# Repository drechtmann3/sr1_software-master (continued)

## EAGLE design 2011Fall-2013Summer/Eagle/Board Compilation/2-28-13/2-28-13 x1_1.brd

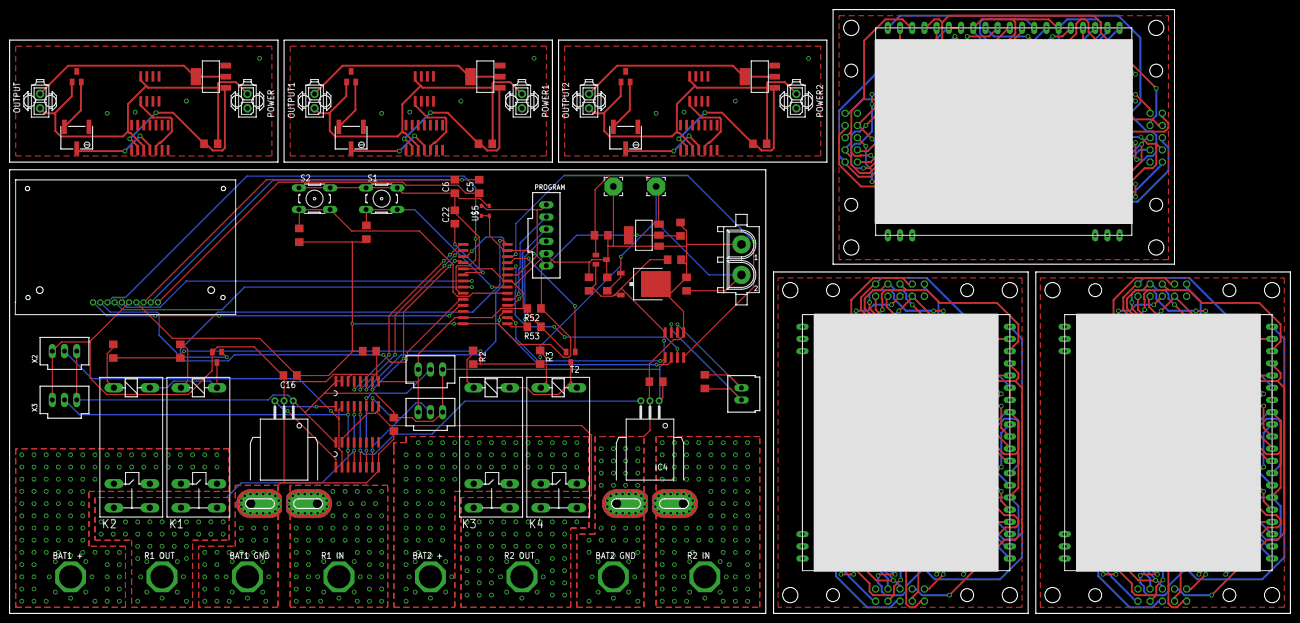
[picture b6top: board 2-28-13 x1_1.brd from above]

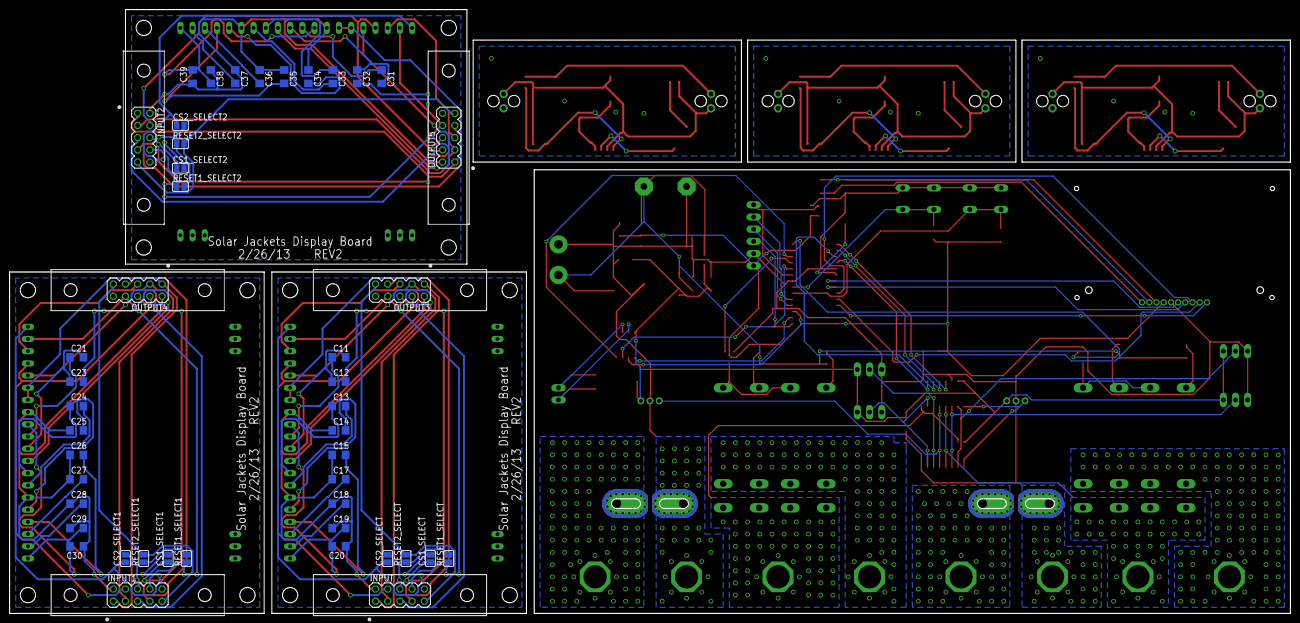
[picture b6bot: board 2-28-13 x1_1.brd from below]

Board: 2 copper layers, 266.7 x 125.7 mm, 130 parts (45 on the bottom side), 136 nets.

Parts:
BAT+_1: BAT1 +; SOLDERPAD
BAT+_2: BAT2 +; SOLDERPAD
BAT-_1: BAT1 GND; SOLDERPAD
BAT-_2: BAT2 GND; SOLDERPAD
C1: .3uF; C1206
C2, C3, C4, C5, C6, C7, C8, C9, C10, C11, C12, C13, C14, C15, C17, C18, C19, C20, C21, C22, C23, C24, C25, C26, C27, C28, C29, C30, C31, C32, C33, C34, C35, C36, C37, C38, C39: 1uF; C1206
C16, C48: .1uF; C1206
CS1_SELECT, CS1_SELECT1, CS1_SELECT2, CS2_SELECT, CS2_SELECT1, CS2_SELECT2: SJ
IC1: 7805DT; TO252
IC2, IC4: ACS758ECB-200B-PFF-T; CB-PFF
IC3: REG1117; SOT223
IC5, IC6, IC7: LM339D; SO14
IC8, IC9, IC10: EADOGM128
INPUT, INPUT1, INPUT2: AMP_LATCH_10; MA05-2
J1: 350428-1
K1, K2, K3, K4: G2REA
OUTPUT, OUTPUT1, OUTPUT2: 794681-2
OUTPUT3, OUTPUT4, OUTPUT5: AMP_LATCH_10; MA05-2
PAD_12V: 12v; 3,81/1,4
PAD_GND: gnd; 3,81/1,4
POWER, POWER1, POWER2: 794681-2
PROGRAM: C-GRID-06-70543; 70543-06
R1, R2, R3, R4, R5, R169: 1K; R1206
R6: 120; R1206
R7, R8, R9: 10k; RTRIMTS63Y
R52: 10k\; R1206
R53: 470; R1206
RESET1_SELECT, RESET1_SELECT1, RESET1_SELECT2, RESET2_SELECT, RESET2_SELECT1, RESET2_SELECT2: SJ
R_IN_1: R1 IN; SOLDERPAD
R_IN_2: R2 IN; SOLDERPAD
R_OUT_1: R1 OUT; SOLDERPAD
R_OUT_2: R2 OUT; SOLDERPAD
S1, S2: B3F-10XX
T1, T2: PMV56XN; SOT23
U$1: MCP-3008; SO16
U$2: LCD_SCREEN
U$3: SP720APP; SO16
U$4: PIC24HJ128GP-202; SO28W
U$5: ASE
U$6: MAX6105; SOT23
U$7: MAX3440E; SO-08
U$8, U$12, U$16: 100; R1206
U$9, U$13, U$17: MAX6103; SOT23
U$10, U$14, U$18: NDT3055; SOT223
U$11, U$15, U$19: LM35; SO-08
X1: BAT2 TEMP 1; 70543-03
X2: BAT1 TEMP1; 70543-03
X3: BAT1 TEMP2; 70543-03
X4: BAT2 TEMP2; 70543-03
X5: rs-485; 70543-02

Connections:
3.3V: IC8.34, IC8.35, INPUT.1, OUTPUT3.1
3.3V1: IC9.34, IC9.35, INPUT1.1, OUTPUT4.1
3.3V2: IC10.34, IC10.35, INPUT2.1, OUTPUT5.1
12V: IC5.3, OUTPUT.1, POWER.2, U$8.2, U$9.1, U$11.8
12V1: IC6.3, OUTPUT1.1, POWER1.2, U$12.2, U$13.1, U$15.8
12V2: IC7.3, OUTPUT2.1, POWER2.2, U$16.2, U$17.1, U$19.8
+3V3: C9.1, C16.1, C48.1, IC3.2, PROGRAM.6, R4.2, R5.1, R52.1, U$2.7, U$4.13, U$4.28, U$5.1, U$5.4
+5V: C3.2, C4.1, C7.1, C10.2, IC1.2, IC2.1, IC4.1, U$1.15, U$1.16, U$3.16, U$6.2, U$7.8, X1.3, X2.3, X3.3, X4.3
+12V: C1.1, C2.1, C8.1, IC1.1, IC3.3, J1.2, PAD_12V.1, R1.2, R2.2, R3.2, R169.2, U$6.1
A0: IC8.38, INPUT.5, OUTPUT3.5
A1: IC9.38, INPUT1.5, OUTPUT4.5
A2: IC10.38, INPUT2.5, OUTPUT5.5
CH0: IC2.3, U$1.1, U$3.1
CH1: U$1.2, U$3.2, X2.2
CH2: U$1.3, U$3.3, X3.2
CH3: K1.S, K1.S@, K2.S, K2.S@, R_OUT_1.P$1, U$1.4, U$3.4
CH4: IC4.3, U$1.5, U$3.5
CH5: U$1.6, U$3.6, X1.2
CH6: U$1.7, U$3.7, X4.2
CH7: K3.S, K3.S@, K4.S, K4.S@, R_OUT_2.P$1, U$1.8, U$3.15
CS1: CS1_SELECT.1, INPUT.6, OUTPUT3.6
CS2: CS2_SELECT.2, INPUT.7, OUTPUT3.7
CS3: CS1_SELECT1.1, INPUT1.6, OUTPUT4.6
CS4: CS2_SELECT1.2, INPUT1.7, OUTPUT4.7
CS5: CS1_SELECT2.1, INPUT2.6, OUTPUT5.6
CS6: CS2_SELECT2.2, INPUT2.7, OUTPUT5.7
CS_SLCT: CS1_SELECT.2, CS2_SELECT.1, IC8.40
CS_SLCT1: CS1_SELECT1.2, CS2_SELECT1.1, IC9.40
CS_SLCT2: CS1_SELECT2.2, CS2_SELECT2.1, IC10.40
GND: BAT-_1.P$1, BAT-_2.P$1, C1.2, C2.2, C3.1, C4.2, C6.1, C7.2, C8.2, C9.2, C10.1, C16.2, C22.2, C48.2, IC1.3, IC2.2, IC2.IP+, IC2.IP+@2, IC2.IP+@3, IC2.IP+@4, IC2.IP+@5, IC2.IP+@6, IC2.IP+@7, IC2.IP+@8, IC2.IP+@9, IC2.IP+@10, IC2.IP+@11, IC2.IP+@12, IC2.IP+@13, IC2.IP+@14, IC2.IP+@15, IC2.IP+@16, IC2.IP+@17, IC3.1, IC4.2, IC4.IP+, IC4.IP+@2, IC4.IP+@3, IC4.IP+@4, IC4.IP+@5, IC4.IP+@6, IC4.IP+@7, IC4.IP+@8, IC4.IP+@9, IC4.IP+@10, IC4.IP+@11, IC4.IP+@12, IC4.IP+@13, IC4.IP+@14, IC4.IP+@15, IC4.IP+@16, IC4.IP+@17, J1.1, PAD_GND.1, PROGRAM.5, R52.2, R53.1, S1.1, S1.2, S2.1, S2.2, T1.2, T2.2, U$1.9, U$1.14, U$2.6, U$3.8, U$4.8, U$4.19, U$4.27, U$5.2, U$6.3, U$7.5, X1.1, X2.1, X3.1, X4.1
GND1: IC5.12, POWER.1, R7.1, U$9.3, U$10.3, U$11.4
GND2: IC6.12, POWER1.1, R8.1, U$13.3, U$14.3, U$15.4
GND3: IC7.12, POWER2.1, R9.1, U$17.3, U$18.3, U$19.4
GND4: C14.1, C15.1, C17.1, C18.1, C19.1, C20.1, IC8.26, IC8.33, INPUT.2, OUTPUT3.2
GND5: C25.1, C26.1, C27.1, C28.1, C29.1, C30.1, IC9.26, IC9.33, INPUT1.2, OUTPUT4.2
GND6: C34.1, C35.1, C36.1, C37.1, C38.1, C39.1, IC10.26, IC10.33, INPUT2.2, OUTPUT5.2
MCLR: PROGRAM.4, R53.2, U$4.1
unnamed: K1.2, K2.2, T1.3
unnamed: K2.1, R1.1
unnamed: BAT+_2.P$1, K3.P, K3.P@, K4.P, K4.P@
unnamed: K3.1, R2.1
unnamed: K3.2, K4.2, T2.3
unnamed: K4.1, R3.1
unnamed: IC4.IP-, IC4.IP-@2, IC4.IP-@3, IC4.IP-@4, IC4.IP-@5, IC4.IP-@6, IC4.IP-@7, IC4.IP-@8, IC4.IP-@9, IC4.IP-@10, IC4.IP-@11, IC4.IP-@12, IC4.IP-@13, IC4.IP-@14, IC4.IP-@15, IC4.IP-@16, IC4.IP-@17, R_IN_2.P$1
unnamed: IC2.IP-, IC2.IP-@2, IC2.IP-@3, IC2.IP-@4, IC2.IP-@5, IC2.IP-@6, IC2.IP-@7, IC2.IP-@8, IC2.IP-@9, IC2.IP-@10, IC2.IP-@11, IC2.IP-@12, IC2.IP-@13, IC2.IP-@14, IC2.IP-@15, IC2.IP-@16, IC2.IP-@17, R_IN_1.P$1
unnamed: C6.2, U$2.8
unnamed: C5.2, U$2.9
unnamed: C5.1, U$2.10
unnamed: IC5.2, U$8.1, U$10.1
unnamed: C22.1, U$4.20
unnamed: IC5.4, R7.2
unnamed: R7.3, U$9.2
unnamed: OUTPUT.2, U$10.2, U$10.4
unnamed: IC5.5, U$11.1
unnamed: IC6.2, U$12.1, U$14.1
unnamed: IC6.4, R8.2
unnamed: R8.3, U$13.2
unnamed: OUTPUT1.2, U$14.2, U$14.4
unnamed: IC6.5, U$15.1
unnamed: IC7.2, U$16.1, U$18.1
unnamed: IC7.4, R9.2
unnamed: R9.3, U$17.2
unnamed: OUTPUT2.2, U$18.2, U$18.4
unnamed: IC7.5, U$19.1
unnamed: C11.2, C12.1, IC8.30
unnamed: C11.1, IC8.31
unnamed: C12.2, IC8.29
unnamed: C13.2, IC8.27
unnamed: C13.1, IC8.28
unnamed: C14.2, IC8.25
unnamed: C15.2, IC8.24
unnamed: C17.2, IC8.23
unnamed: C18.2, IC8.22
unnamed: C19.2, IC8.21
unnamed: C20.2, IC8.32
unnamed: C21.2, C23.1, IC9.30
unnamed: C21.1, IC9.31
unnamed: C23.2, IC9.29
unnamed: C24.2, IC9.27
unnamed: C24.1, IC9.28
unnamed: C25.2, IC9.25
unnamed: C26.2, IC9.24
unnamed: C27.2, IC9.23
unnamed: C28.2, IC9.22
unnamed: C29.2, IC9.21
unnamed: C30.2, IC9.32
unnamed: C31.2, C32.1, IC10.30
unnamed: C31.1, IC10.31
unnamed: C32.2, IC10.29
unnamed: K1.1, R169.1
unnamed: C33.2, IC10.27
unnamed: C33.1, IC10.28
unnamed: C34.2, IC10.25
unnamed: C35.2, IC10.24
unnamed: C36.2, IC10.23
unnamed: C37.2, IC10.22
unnamed: C38.2, IC10.21
unnamed: C39.2, IC10.32
unnamed: R6.2, U$7.7, X5.1
unnamed: R6.1, U$7.6, X5.2
unnamed: BAT+_1.P$1, K1.P, K1.P@, K2.P, K2.P@
OSC1: PROGRAM.1, U$4.9, U$5.3
PGEC1: PROGRAM.2, U$4.5
PGED1: PROGRAM.3, U$4.4
RA0: U$4.2, U$7.1
RA1: U$4.3, U$7.2
RA3: U$4.10, U$7.3
RA4: U$4.12, U$7.4
RB2: R5.2, S2.3, S2.4, U$4.6
RB3: R4.1, S1.3, S1.4, U$4.7
RB4: T2.1, U$4.11
RB5: T1.1, U$4.14
RB6: U$1.13, U$4.15
RB7: U$1.12, U$4.16
RB8: U$1.11, U$4.17
RB9: U$1.10, U$4.18
RB10: U$2.5, U$4.21
RB11: U$2.4, U$4.22
RB12: U$2.3, U$4.23
RB13: U$2.2, U$4.24
RB14: U$2.1, U$4.25
RESET1: IC8.39, INPUT.8, OUTPUT3.8, RESET1_SELECT.1
RESET2: INPUT.9, OUTPUT3.9, RESET2_SELECT.2
RESET3: IC9.39, INPUT1.8, OUTPUT4.8, RESET1_SELECT1.1
RESET4: INPUT1.9, OUTPUT4.9, RESET2_SELECT1.2
RESET5: IC10.39, INPUT2.8, OUTPUT5.8, RESET1_SELECT2.1
RESET6: INPUT2.9, OUTPUT5.9, RESET2_SELECT2.2
RESET_SLCT: RESET1_SELECT.2, RESET2_SELECT.1
RESET_SLCT1: RESET1_SELECT1.2, RESET2_SELECT1.1
RESET_SLCT2: RESET1_SELECT2.2, RESET2_SELECT2.1
SCL: IC8.37, INPUT.4, OUTPUT3.4
SCL1: IC9.37, INPUT1.4, OUTPUT4.4
SCL2: IC10.37, INPUT2.4, OUTPUT5.4
SI: IC8.36, INPUT.3, OUTPUT3.3
SI1: IC9.36, INPUT1.3, OUTPUT4.3
SI2: IC10.36, INPUT2.3, OUTPUT5.3

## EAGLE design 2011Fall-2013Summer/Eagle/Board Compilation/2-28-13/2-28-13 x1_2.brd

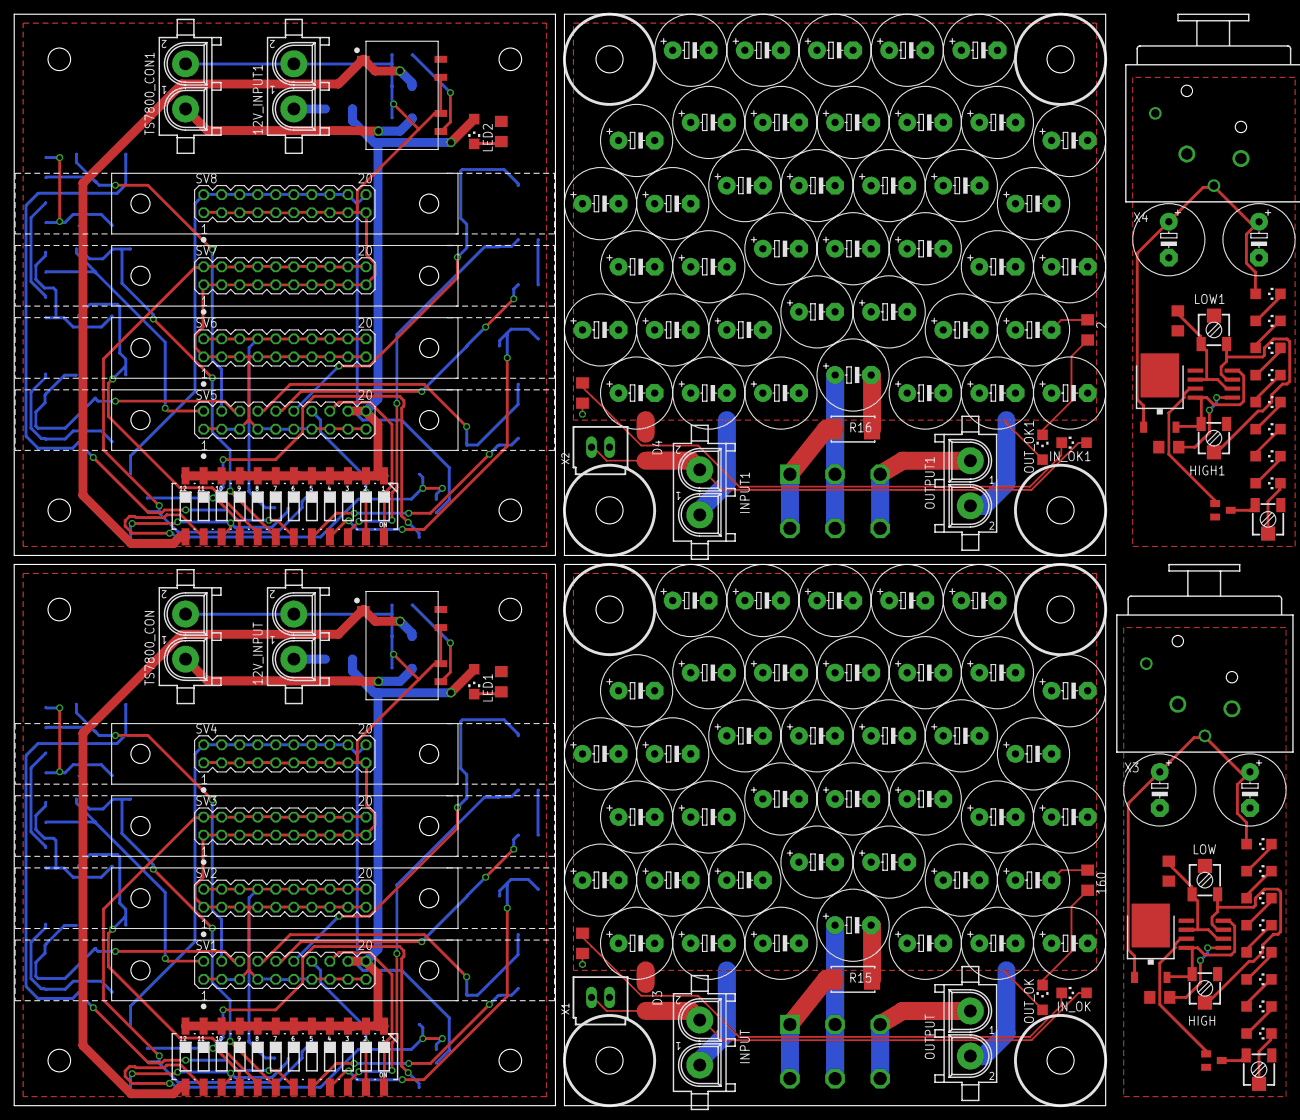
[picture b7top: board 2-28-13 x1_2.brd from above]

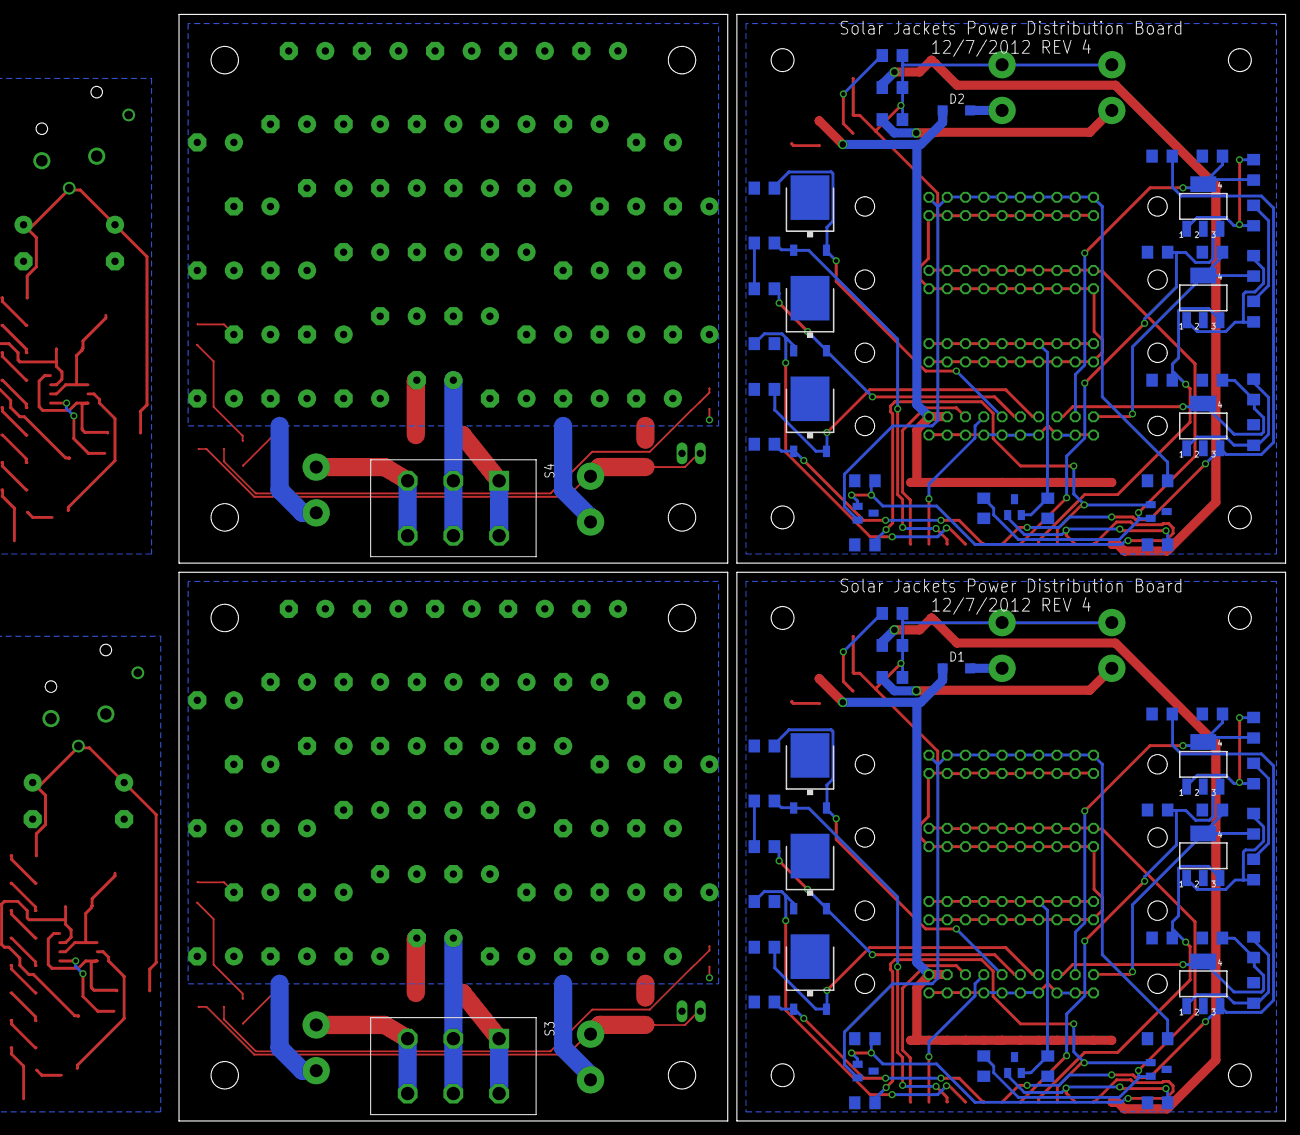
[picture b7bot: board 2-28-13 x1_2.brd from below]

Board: 2 copper layers, 153.7 x 153.7 mm, 232 parts (76 on the bottom side), 106 nets.

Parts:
1, 3: 160; R1206
1K, 1K1: 10 k; RTRIM3314J
2, 160: R1206
3V1, 3V2, 3V3, 3V4, 3V5, 3V6: MAX6103; SOT23
12V_INPUT, 12V_INPUT1: 350759-4
317CAP1, 317CAP3, 317CAP4, 317CAP6, 317CAP9, 317CAP11: .33uF; C1206
317CAP2, 317CAP5, 317CAP7, 317CAP8, 317CAP10, 317CAP12, 6103CAP1, 6103CAP2, 6103CAP3, 6103CAP4, 6103CAP5, 6103CAP6, 6103CAP7, 6103CAP8, 6103CAP9, 6103CAP10, 6103CAP11, 6103CAP12: 1uF; C1206
C1, C2, C3, C4, C5, C6, C7, C8, C9, C10, C11, C12: 1uF; C1206
C13, C14, C15, C16, C17, C18, C19, C20, C21, C22, C23, C24, C25, C26, C27, C28, C29, C30, C31, C32, C33, C34, C35, C36, C37, C38, C39, C40, C41, C42, C43, C44, C45, C46, C47, C48, C49, C50, C51, C52, C53, C54, C55, C56, C57, C58, C59, C60, C61, C62, C63, C64, C65, C66, C67, C68, C69, C70, C71, C72, C73, C74, C75, C76, C77, C78, C79, C80, C81, C82, C83, C84, C85, C86, C87, C88, C89, C90, C91, C92: E5-10,5
C93, C97: 100uF; C1206
C94, C98: 10nF; C1206
C95, C96, C99, C100: 2.2F; E5-10,5
D1, D2, D3, D4: SOD123
HIGH, HIGH1: 10k; RTRIM3314J
IC1, IC2, IC3, IC4, IC5, IC6: LM317; SOT223
IC7, IC9: 7805DT; TO252
IC8, IC10: LM555D; SO08
INPUT, INPUT1: 350428-1
IN_OK, IN_OK1: CHIPLED_1206
LED1, LED2, LED3, LED4, LED5, LED6, LED7, LED8, LED9, LED10, LED11, LED12, LED13, LED14, LED15, LED16, LED17, LED18: CHIPLED_1206
LOW, LOW1: 10k; RTRIM3314J
OUTPUT, OUTPUT1: 350428-1
OUT_OK, OUT_OK1: CHIPLED_1206
PWR_1, PWR_2, PWR_3, PWR_4, PWR_5, PWR_6: 7805DT; TO252
R1, R14: 430; R1206
R2, R4, R6, R7, R9, R11: 220; R1206
R3, R5, R8, R10, R12, R13: 361; R1206
R15, R16: 50 1W; WSC2515
S1, S2: 219-12; CTS-219-12
S3, S4: SLIDE_SWITCH
SV1, SV2, SV3, SV4, SV5, SV6, SV7, SV8: AMPLATCH-20; MA10-2
TS7800_CON, TS7800_CON1: 350759-4
U$1, U$2: V7805
U$3, U$4: PMV56XN215; SOT23
V7805_C1, V7805_C2, V7805_C3, V7805_C4, V7805_C5, V7805_C6: 1uF; C1206
X1, X2: C-GRID-02-70543; 70543-02
X3, X4: NC3FAH2

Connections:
3.3V1: 317CAP8.1, IC4.4, R7.1, SV1.6
3.3V1_EN: 317CAP3.1, IC4.3, S1.19
3.3V1_EN1: 317CAP1.1, IC1.3, S2.19
3.3V2: 317CAP10.1, IC5.4, R9.1, SV1.4
3.3V2_EN: 317CAP9.1, IC5.3, S1.18
3.3V2_EN1: 317CAP4.1, IC2.3, S2.18
3.3V3: 317CAP12.1, IC6.4, R11.1, SV1.2
3.3V3_EN: 317CAP11.1, IC6.3, S1.17
3.3V3_EN1: 317CAP6.1, IC3.3, S2.17
3.3V4: 317CAP7.1, IC3.4, R6.1, SV5.2
3.3V5: 317CAP2.1, IC1.4, R2.1, SV5.6
3.3V6: 317CAP5.1, IC2.4, R4.1, SV5.4
5V: C13.+, C14.+, C15.+, C16.+, C17.+, C18.+, C19.+, C20.+, C21.+, C22.+, C23.+, C24.+, C25.+, C26.+, C27.+, C28.+, C29.+, C30.+, C31.+, C32.+, C33.+, C34.+, C35.+, C36.+, C37.+, C38.+, C39.+, C40.+, C41.+, C42.+, C43.+, C44.+, C45.+, C46.+, C47.+, C48.+, C49.+, C50.+, C51.+, C52.+, D3.C, OUT_OK.A, S3.2, S3.5
5V1: C2.1, PWR_1.2, SV1.12
5V1_EN: C1.1, PWR_1.1, S1.22
5V1_EN1: C7.1, PWR_4.1, S2.22
5V2: C4.1, PWR_2.2, SV1.10
5V2_EN: C3.1, PWR_2.1, S1.21
5V2_EN1: C9.1, PWR_5.1, S2.21
5V3: C6.1, PWR_3.2, SV1.8
5V3_EN: C5.1, PWR_3.1, S1.20
5V3_EN1: C12.1, PWR_6.1, S2.20
5V4: C11.1, PWR_6.2, SV5.8
5V5: C10.1, PWR_5.2, SV5.10
5V6: C8.1, PWR_4.2, SV5.12
5V7: C53.+, C54.+, C55.+, C56.+, C57.+, C58.+, C59.+, C60.+, C61.+, C62.+, C63.+, C64.+, C65.+, C66.+, C67.+, C68.+, C69.+, C70.+, C71.+, C72.+, C73.+, C74.+, C75.+, C76.+, C77.+, C78.+, C79.+, C80.+, C81.+, C82.+, C83.+, C84.+, C85.+, C86.+, C87.+, C88.+, C89.+, C90.+, C91.+, C92.+, D4.C, OUT_OK1.A, S4.2, S4.5
12V: D1.C, LED1.A, S1.1, S1.2, S1.3, S1.4, S1.5, S1.6, S1.7, S1.8, S1.9, S1.10, S1.11, S1.12, SV1.18, SV1.20
12V1: D2.C, LED2.A, S2.1, S2.2, S2.3, S2.4, S2.5, S2.6, S2.7, S2.8, S2.9, S2.10, S2.11, S2.12, SV5.18, SV5.20
12V1_EN: S1.24, SV1.16
12V1_EN1: S2.24, SV5.16
12V2_EN: S1.23, SV1.14
12V2_EN1: S2.23, SV5.14
24V: C95.+, C96.+, IC7.1, LED3.A, X3.3
24V1: C99.+, C100.+, IC9.1, LED11.A, X4.3
+5V: HIGH.3, IC7.2, IC8.4, IC8.8
+5V1: HIGH1.3, IC9.2, IC10.4, IC10.8
GND: 3V3.3, 3V4.3, 3V5.3, 12V_INPUT.2, 317CAP3.2, 317CAP8.2, 317CAP9.2, 317CAP10.2, 317CAP11.2, 317CAP12.2, 6103CAP7.2, 6103CAP8.2, 6103CAP9.2, 6103CAP10.2, 6103CAP11.2, 6103CAP12.2, C1.2, C2.2, C3.2, C4.2, C5.2, C6.2, PWR_1.3, PWR_2.3, PWR_3.3, R1.2, R8.2, R10.2, R12.2, SV1.1, SV1.3, SV1.5, SV1.7, SV1.9, SV1.11, SV1.13, SV1.15, SV1.17, SV1.19, SV2.1, SV2.3, SV2.5, SV2.7, SV2.9, SV2.11, SV2.13, SV2.15, SV2.17, SV2.19, SV3.1, SV3.3, SV3.5, SV3.7, SV3.9, SV3.11, SV3.13, SV3.15, SV3.17, SV3.19, SV4.1, SV4.3, SV4.5, SV4.7, SV4.9, SV4.11, SV4.13, SV4.15, SV4.17, SV4.19, TS7800_CON.2, U$2.7, U$2.9, V7805_C4.2, V7805_C5.2, V7805_C6.2
GND1: 3V1.3, 3V2.3, 3V6.3, 12V_INPUT1.2, 317CAP1.2, 317CAP2.2, 317CAP4.2, 317CAP5.2, 317CAP6.2, 317CAP7.2, 6103CAP1.2, 6103CAP2.2, 6103CAP3.2, 6103CAP4.2, 6103CAP5.2, 6103CAP6.2, C7.2, C8.2, C9.2, C10.2, C11.2, C12.2, PWR_4.3, PWR_5.3, PWR_6.3, R3.2, R5.2, R13.2, R14.2, SV5.1, SV5.3, SV5.5, SV5.7, SV5.9, SV5.11, SV5.13, SV5.15, SV5.17, SV5.19, SV6.1, SV6.3, SV6.5, SV6.7, SV6.9, SV6.11, SV6.13, SV6.15, SV6.17, SV6.19, SV7.1, SV7.3, SV7.5, SV7.7, SV7.9, SV7.11, SV7.13, SV7.15, SV7.17, SV7.19, SV8.1, SV8.3, SV8.5, SV8.7, SV8.9, SV8.11, SV8.13, SV8.15, SV8.17, SV8.19, TS7800_CON1.2, U$1.7, U$1.9, V7805_C1.2, V7805_C2.2, V7805_C3.2
GND2: 1.1, 160.1, C13.-, C14.-, C15.-, C16.-, C17.-, C18.-, C19.-, C20.-, C21.-, C22.-, C23.-, C24.-, C25.-, C26.-, C27.-, C28.-, C29.-, C30.-, C31.-, C32.-, C33.-, C34.-, C35.-, C36.-, C37.-, C38.-, C39.-, C40.-, C41.-, C42.-, C43.-, C44.-, C45.-, C46.-, C47.-, C48.-, C49.-, C50.-, C51.-, C52.-, INPUT.1, OUTPUT.2, R15.2
GND3: 2.1, 3.1, C53.-, C54.-, C55.-, C56.-, C57.-, C58.-, C59.-, C60.-, C61.-, C62.-, C63.-, C64.-, C65.-, C66.-, C67.-, C68.-, C69.-, C70.-, C71.-, C72.-, C73.-, C74.-, C75.-, C76.-, C77.-, C78.-, C79.-, C80.-, C81.-, C82.-, C83.-, C84.-, C85.-, C86.-, C87.-, C88.-, C89.-, C90.-, C91.-, C92.-, INPUT1.1, OUTPUT1.2, R16.2
GND4: C93.2, C94.2, C95.-, C96.-, IC7.3, IC8.1, U$3.2, X3.1
GND5: C97.2, C98.2, C99.-, C100.-, IC9.3, IC10.1, U$4.2, X4.1
unnamed: U$2.6, V7805_C4.1
unnamed: LED1.C, R1.1
unnamed: 12V_INPUT.1, D1.A
unnamed: IC1.1, R2.2, R3.1
unnamed: IC2.1, R4.2, R5.1
unnamed: IC3.1, R6.2, R13.1
unnamed: U$1.6, V7805_C1.1
unnamed: LED2.C, R14.1
unnamed: 12V_INPUT1.1, D2.A
unnamed: 160.2, OUT_OK.C
unnamed: OUTPUT.1, S3.3, S3.4
unnamed: IC4.1, R7.2, R8.1
unnamed: IC5.1, R9.2, R10.1
unnamed: IC6.1, R11.2, R12.1
unnamed: D3.A, INPUT.2, IN_OK.A, X1.1
unnamed: R15.1, S3.1, S3.6
unnamed: 1.2, IN_OK.C
unnamed: 2.2, OUT_OK1.C
unnamed: OUTPUT1.1, S4.3, S4.4
unnamed: D4.A, INPUT1.2, IN_OK1.A, X2.1
unnamed: R16.1, S4.1, S4.6
unnamed: 3.2, IN_OK1.C
unnamed: LED3.C, LED4.A
unnamed: LED4.C, LED5.A
unnamed: LED5.C, LED6.A
unnamed: LED6.C, LED7.A
unnamed: LED7.C, LED9.A
unnamed: LED8.A, LED9.C
unnamed: LED8.C, LED10.A
unnamed: 1K.2, LED10.C
unnamed: HIGH.2, IC8.7, LOW.3
unnamed: C93.1, IC8.2, IC8.6, LOW.1
unnamed: C94.1, IC8.5
unnamed: 1K.3, U$3.3
unnamed: IC8.3, U$3.1
unnamed: LED11.C, LED12.A
unnamed: LED12.C, LED13.A
unnamed: LED13.C, LED14.A
unnamed: LED14.C, LED15.A
unnamed: LED15.C, LED17.A
unnamed: LED16.A, LED17.C
unnamed: LED16.C, LED18.A
unnamed: 1K1.2, LED18.C
unnamed: HIGH1.2, IC10.7, LOW1.3
unnamed: C97.1, IC10.2, IC10.6, LOW1.1
unnamed: C98.1, IC10.5
unnamed: 1K1.3, U$4.3
unnamed: IC10.3, U$4.1
TS7800_+: TS7800_CON.1, U$2.5, V7805_C6.1
TS7800_+1: TS7800_CON1.1, U$1.5, V7805_C3.1
TS7800_EN: S1.13, U$2.1, V7805_C5.1
TS7800_EN1: S2.13, U$1.1, V7805_C2.1
VREF1: 3V3.2, 6103CAP8.1, SV3.2, SV3.4, SV3.6, SV3.8, SV3.10, SV3.12, SV3.14, SV3.16, SV3.18, SV3.20
VREF1_EN: 3V3.1, 6103CAP7.1, S1.16
VREF1_EN1: 3V1.1, 6103CAP1.1, S2.16
VREF2: 3V4.2, 6103CAP10.1, SV2.2, SV2.4, SV2.6, SV2.8, SV2.10, SV2.12, SV2.14, SV2.16, SV2.18, SV2.20
VREF2_EN: 3V4.1, 6103CAP9.1, S1.15
VREF2_EN1: 3V2.1, 6103CAP3.1, S2.15
VREF3: 3V5.2, 6103CAP12.1, SV4.2, SV4.4, SV4.6, SV4.8, SV4.10, SV4.12, SV4.14, SV4.16, SV4.18, SV4.20
VREF3_EN: 3V5.1, 6103CAP11.1, S1.14
VREF3_EN1: 3V6.1, 6103CAP5.1, S2.14
VREF4: 3V1.2, 6103CAP2.1, SV7.2, SV7.4, SV7.6, SV7.8, SV7.10, SV7.12, SV7.14, SV7.16, SV7.18, SV7.20
VREF5: 3V2.2, 6103CAP4.1, SV6.2, SV6.4, SV6.6, SV6.8, SV6.10, SV6.12, SV6.14, SV6.16, SV6.18, SV6.20
VREF6: 3V6.2, 6103CAP6.1, SV8.2, SV8.4, SV8.6, SV8.8, SV8.10, SV8.12, SV8.14, SV8.16, SV8.18, SV8.20

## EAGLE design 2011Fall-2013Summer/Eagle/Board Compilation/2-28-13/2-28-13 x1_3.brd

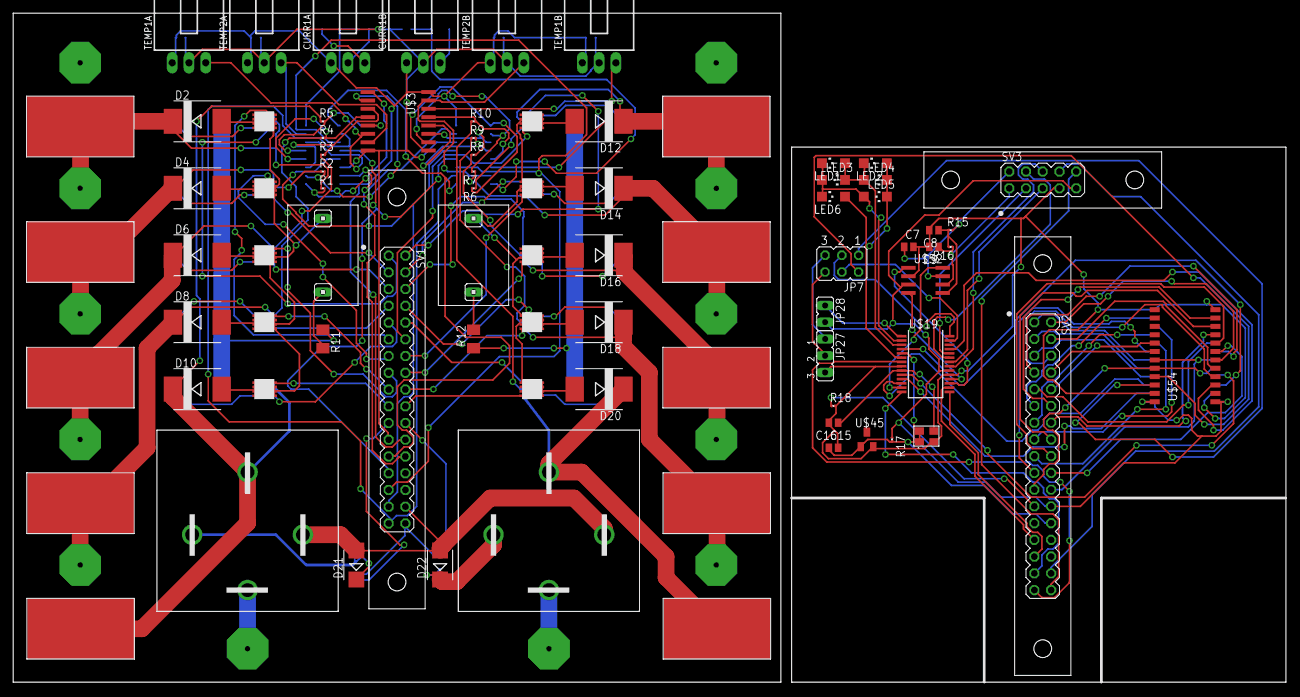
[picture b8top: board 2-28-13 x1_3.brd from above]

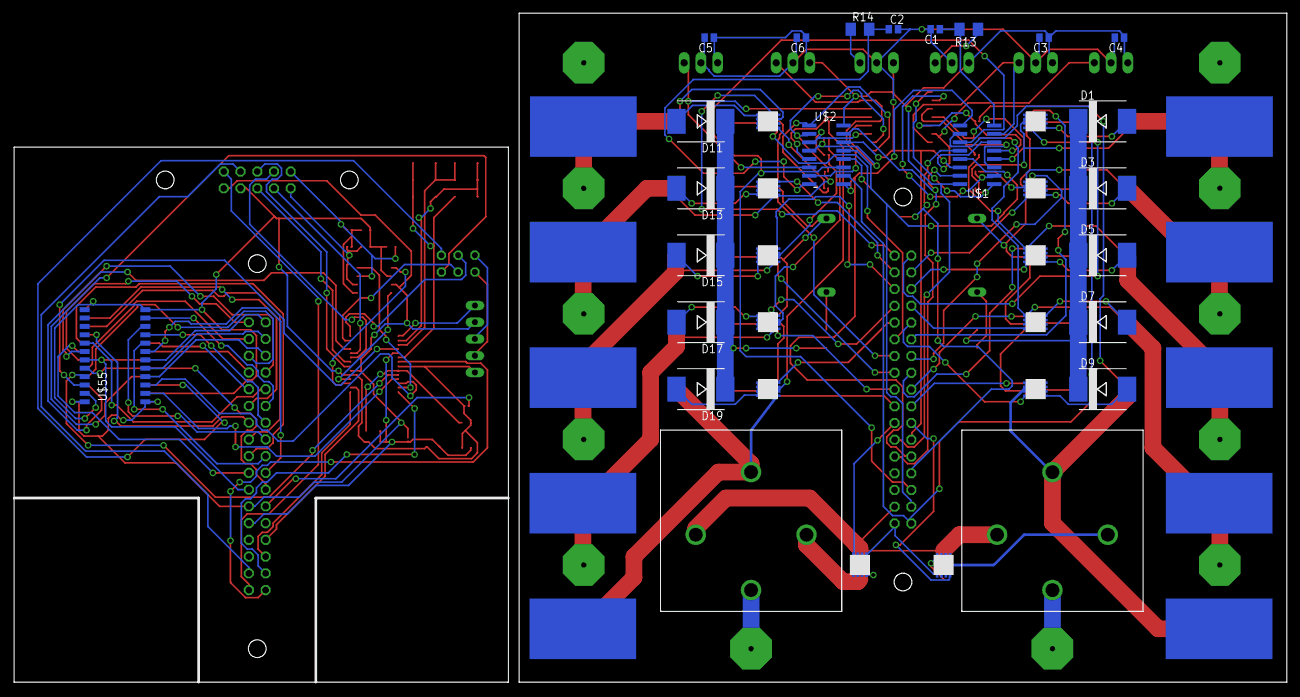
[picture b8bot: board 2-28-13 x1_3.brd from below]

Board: 2 copper layers, 193.1 x 101.5 mm, 126 parts (33 on the bottom side), 148 nets.

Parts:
C1, C2, C3, C4, C5, C6: 0.1uF; C0504
C7, C9: 100pF; C0504
C8: 47nF; C0504
C15: 10nF; C0504
C16: 15pF; C0504
CURR1A, CURR1B: C-GRID-03-70553; 70553-03
D1, D2, D3, D4, D5, D6, D7, D8, D9, D10, D11, D12, D13, D14, D15, D16, D17, D18, D19, D20: SMC
D21, D22: SMB
JP7: JP3Q
JP27: JP2
JP28: JP1
L1, L2: INDUCTOR_SOCKET
LED1, LED2, LED3, LED4, LED5, LED6: CHIPLED_1206
R1, R2, R3, R4, R5, R6, R7, R8, R9, R10: 3.3M; R0201
R11, R12: M1206
R13, R14: 1K; M1206
R15, R16: 1k3; R0201
R17: 150; R0201
R18: 0; R0201
SV1, SV2: MA17-2
SV3: AMP_LATCH_10; MA05-2
TEMP1A, TEMP1B, TEMP2A, TEMP2B: C-GRID-03-70553; 70553-03
U$1, U$2: MCP3008; SOIC16N
U$3: SP720APP; SO16W
U$4, U$5, U$6, U$7, U$8, U$9, U$10, U$11, U$12, U$13, U$23, U$26, U$27, U$30, U$31, U$32, U$33, U$34, U$35, U$36, U$37, U$38: SIS322DNT-T1-GE3POWERPAK1212-8; POWERPAK1212-8
U$14, U$15, U$16, U$17, U$18, U$40, U$41, U$42, U$43, U$44: MOLEXCONN-SCREWHOLE
U$19: PIC18F23K22; SSOP28
U$20, U$22, U$24, U$25, U$28, U$29, U$46, U$47, U$48, U$49, U$50, U$51: MOLEXCONN-SCREWHOLE-NEG
U$21, U$39: PB1039
U$45: LM4040; SOT23
U$52: TJA1040; SO-08
U$53: CTS632
U$54, U$55: CD4514BM96E4; SOIC-24

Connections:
12V+: SV1.34, U$23.SOURCE1, U$23.SOURCE2, U$23.SOURCE3, U$38.SOURCE1, U$38.SOURCE2, U$38.SOURCE3
12V+1: SV2.34, SV3.10
12V-: D21.A, D22.A, SV1.32, U$21.P$2, U$39.P$2
12V-1: SV2.32, SV3.8
AGND_PLANE: C1.2, C2.2, C3.2, C4.2, C5.2, C6.2, CURR1A.2, CURR1B.2, SV1.23, TEMP1A.2, TEMP1B.2, TEMP2A.2, TEMP2B.2, U$1.14, U$2.14, U$3.8
AGND_PLANE1: R18.1, SV2.23
CAN: U$19.13, U$52.8
CANH: C7.1, R15.2, SV3.2, U$52.7
CANL: C9.1, R16.1, SV3.1, U$52.6
CH0A: D2.C, R1.1, U$4.SOURCE1, U$4.SOURCE2, U$4.SOURCE3, U$14.P$1, U$22.P$1
CH0B: D12.C, R6.1, U$26.SOURCE1, U$26.SOURCE2, U$26.SOURCE3, U$40.P$1, U$47.P$1
CH1A: D4.C, R2.1, U$6.SOURCE1, U$6.SOURCE2, U$6.SOURCE3, U$15.P$1, U$24.P$1
CH1B: D14.C, R7.1, U$30.SOURCE1, U$30.SOURCE2, U$30.SOURCE3, U$41.P$1, U$48.P$1
CH2A: D6.C, R3.1, U$8.SOURCE1, U$8.SOURCE2, U$8.SOURCE3, U$16.P$1, U$25.P$1
CH2B: D16.C, R8.1, U$32.SOURCE1, U$32.SOURCE2, U$32.SOURCE3, U$42.P$1, U$49.P$1
CH3A: D8.C, R4.1, U$10.SOURCE1, U$10.SOURCE2, U$10.SOURCE3, U$17.P$1, U$28.P$1
CH3B: D18.C, R9.1, U$34.SOURCE1, U$34.SOURCE2, U$34.SOURCE3, U$43.P$1, U$50.P$1
CH4A: D10.C, R5.1, U$12.SOURCE1, U$12.SOURCE2, U$12.SOURCE3, U$18.P$1, U$21.P$4
CH4B: D20.C, R10.1, U$36.SOURCE1, U$36.SOURCE2, U$36.SOURCE3, U$39.P$4, U$44.P$1
CH5A: TEMP1A.3, U$1.6, U$3.6
CH5B: TEMP1B.3, U$2.6, U$3.14
CH6A: TEMP2A.3, U$1.7, U$3.7
CH6B: TEMP2B.3, U$2.7, U$3.15
CH7A: C1.1, R13.2, U$1.8
CH7B: C2.1, R14.2, U$2.8
CLK: SV1.31, U$1.13, U$2.13
CLK1: SV2.31, U$19.14
CS: SV1.33, U$1.10, U$2.10
CS1: SV2.33, U$19.7
DGND: SV1.25, U$1.9, U$2.9
DIN: SV1.29, U$1.11, U$2.11
DIN1: SV2.29, U$19.15
DOUT: SV1.27, U$1.12, U$2.12
DOUT1: SV2.27, U$19.16
GND: C7.2, C8.2, C9.2, C15.2, C16.2, JP27.3, R18.2, SV3.7, U$19.8, U$19.19, U$45.2, U$52.2, U$53.2, U$54.12, U$54.23, U$55.12, U$55.23
I2C_CS: SV3.6, U$19.21
I2C_SCL: SV3.5, U$19.22
I2C_SDI: SV3.4, U$19.23
I2C_SDO: SV3.3, U$19.24
unnamed: R5.2, U$1.5, U$3.5
unnamed: R4.2, U$1.4, U$3.4
unnamed: R3.2, U$1.3, U$3.3
unnamed: R2.2, U$1.2, U$3.2
unnamed: R1.2, U$1.1, U$3.1
unnamed: CURR1A.3, R13.1
unnamed: CURR1B.3, R14.1
unnamed: D1.A, U$4.DRAIN5, U$4.DRAIN6, U$4.DRAIN7, U$4.DRAIN8, U$4.DRAIN_ALL
unnamed: LED1.A, LED2.C, LED3.C, LED4.A, U$19.3
unnamed: LED1.C, LED3.A, LED5.A, LED6.C, U$19.2
unnamed: R10.2, U$2.5, U$3.13
unnamed: R9.2, U$2.4, U$3.12
unnamed: R8.2, U$2.3, U$3.11
unnamed: R7.2, U$2.2, U$3.10
unnamed: R6.2, U$2.1, U$3.9
unnamed: D2.A, U$5.DRAIN5, U$5.DRAIN6, U$5.DRAIN7, U$5.DRAIN8, U$5.DRAIN_ALL
unnamed: D21.C, U$21.P$3, U$23.DRAIN5, U$23.DRAIN6, U$23.DRAIN7, U$23.DRAIN8, U$23.DRAIN_ALL
unnamed: L1.P$1, R11.2
unnamed: LED2.A, LED4.C, LED5.C, LED6.A, U$19.6
unnamed: U$19.18, U$52.4
unnamed: U$19.17, U$52.1
unnamed: JP28.1, U$19.1
unnamed: D3.A, U$6.DRAIN5, U$6.DRAIN6, U$6.DRAIN7, U$6.DRAIN8, U$6.DRAIN_ALL
unnamed: D4.A, U$7.DRAIN5, U$7.DRAIN6, U$7.DRAIN7, U$7.DRAIN8, U$7.DRAIN_ALL
unnamed: U$21.P$1, U$29.P$1
unnamed: D11.A, U$26.DRAIN5, U$26.DRAIN6, U$26.DRAIN7, U$26.DRAIN8, U$26.DRAIN_ALL
unnamed: D5.A, U$8.DRAIN5, U$8.DRAIN6, U$8.DRAIN7, U$8.DRAIN8, U$8.DRAIN_ALL
unnamed: D6.A, U$9.DRAIN5, U$9.DRAIN6, U$9.DRAIN7, U$9.DRAIN8, U$9.DRAIN_ALL
unnamed: D12.A, U$27.DRAIN5, U$27.DRAIN6, U$27.DRAIN7, U$27.DRAIN8, U$27.DRAIN_ALL
unnamed: U$19.4, U$55.22
unnamed: D7.A, U$10.DRAIN5, U$10.DRAIN6, U$10.DRAIN7, U$10.DRAIN8, U$10.DRAIN_ALL
unnamed: D8.A, U$11.DRAIN5, U$11.DRAIN6, U$11.DRAIN7, U$11.DRAIN8, U$11.DRAIN_ALL
unnamed: D13.A, U$30.DRAIN5, U$30.DRAIN6, U$30.DRAIN7, U$30.DRAIN8, U$30.DRAIN_ALL
unnamed: D9.A, U$12.DRAIN5, U$12.DRAIN6, U$12.DRAIN7, U$12.DRAIN8, U$12.DRAIN_ALL
unnamed: D10.A, U$13.DRAIN5, U$13.DRAIN6, U$13.DRAIN7, U$13.DRAIN8, U$13.DRAIN_ALL
unnamed: D14.A, U$31.DRAIN5, U$31.DRAIN6, U$31.DRAIN7, U$31.DRAIN8, U$31.DRAIN_ALL
unnamed: D15.A, U$32.DRAIN5, U$32.DRAIN6, U$32.DRAIN7, U$32.DRAIN8, U$32.DRAIN_ALL
unnamed: D16.A, U$33.DRAIN5, U$33.DRAIN6, U$33.DRAIN7, U$33.DRAIN8, U$33.DRAIN_ALL
unnamed: U$19.10, U$55.21
unnamed: D17.A, U$34.DRAIN5, U$34.DRAIN6, U$34.DRAIN7, U$34.DRAIN8, U$34.DRAIN_ALL
unnamed: D18.A, U$35.DRAIN5, U$35.DRAIN6, U$35.DRAIN7, U$35.DRAIN8, U$35.DRAIN_ALL
unnamed: D19.A, U$36.DRAIN5, U$36.DRAIN6, U$36.DRAIN7, U$36.DRAIN8, U$36.DRAIN_ALL
unnamed: D20.A, U$37.DRAIN5, U$37.DRAIN6, U$37.DRAIN7, U$37.DRAIN8, U$37.DRAIN_ALL
unnamed: L2.P$2, U$27.SOURCE1, U$27.SOURCE2, U$27.SOURCE3, U$31.SOURCE1, U$31.SOURCE2, U$31.SOURCE3, U$33.SOURCE1, U$33.SOURCE2, U$33.SOURCE3, U$35.SOURCE1, U$35.SOURCE2, U$35.SOURCE3, U$37.SOURCE1, U$37.SOURCE2, U$37.SOURCE3
unnamed: U$39.P$1, U$51.P$1
unnamed: D22.C, U$38.DRAIN5, U$38.DRAIN6, U$38.DRAIN7, U$38.DRAIN8, U$38.DRAIN_ALL, U$39.P$3
unnamed: D11.C, D13.C, D15.C, D17.C, D19.C, R12.1
unnamed: L2.P$1, R12.2
unnamed: U$19.11, U$55.2
unnamed: U$19.12, U$55.3
unnamed: JP7.5, JP27.1
unnamed: JP7.6, JP27.2
unnamed: U$19.25, U$54.3
unnamed: JP7.1, U$54.22
unnamed: JP7.2, U$54.21
unnamed: L1.P$2, U$5.SOURCE1, U$5.SOURCE2, U$5.SOURCE3, U$7.SOURCE1, U$7.SOURCE2, U$7.SOURCE3, U$9.SOURCE1, U$9.SOURCE2, U$9.SOURCE3, U$11.SOURCE1, U$11.SOURCE2, U$11.SOURCE3, U$13.SOURCE1, U$13.SOURCE2, U$13.SOURCE3
unnamed: D1.C, D3.C, D5.C, D7.C, D9.C, R11.1
unnamed: C8.1, R15.1, R16.2, U$52.5
unnamed: C16.1, U$19.9, U$53.3
PGC: JP7.4, U$19.27
PGD: JP7.3, U$19.28
RELAYA: SV1.21, U$23.GATE
RELAYA1: SV2.21, U$54.20, U$55.20
RELAYB: SV1.22, U$38.GATE
RELAYB1: SV2.22, U$54.19, U$55.19
VDD_PLANE: C3.1, C4.1, C5.1, C6.1, CURR1A.1, CURR1B.1, SV1.24, TEMP1A.1, TEMP1B.1, TEMP2A.1, TEMP2B.1, U$1.16, U$2.16, U$3.16
VDD_PLANE1: JP28.2, R17.1, SV2.24, SV3.9, U$19.20, U$52.3, U$54.1, U$54.24, U$55.1, U$55.24
VREF: SV1.26, U$1.15, U$2.15
VREF1: C15.1, R17.2, SV2.26, U$19.5, U$45.1, U$53.1, U$53.4
X0A: SV1.1, U$4.GATE
X0A1: SV2.1, U$55.6
X0B: SV1.2, U$26.GATE
X0B1: SV2.2, U$54.6
X1A: SV1.3, U$6.GATE
X1A1: SV2.3, U$55.5
X1B: SV1.4, U$30.GATE
X1B1: SV2.4, U$54.5
X2A: SV1.5, U$8.GATE
X2A1: SV2.5, U$55.4
X2B: SV1.6, U$32.GATE
X2B1: SV2.6, U$54.4
X3A: SV1.7, U$10.GATE
X3A1: SV2.7, U$55.18
X3B: SV1.8, U$34.GATE
X3B1: SV2.8, U$54.18
X4A: SV1.9, U$12.GATE
X4A1: SV2.9, U$55.17
X4B: SV1.10, U$36.GATE
X4B1: SV2.10, U$54.17
Y0A: SV1.11, U$5.GATE
Y0A1: SV2.11, U$55.11
Y0B: SV1.12, U$27.GATE
Y0B1: SV2.12, U$54.11
Y1A: SV1.13, U$7.GATE
Y1A1: SV2.13, U$55.9
Y1B: SV1.14, U$31.GATE
Y1B1: SV2.14, U$54.9
Y2A: SV1.15, U$9.GATE
Y2A1: SV2.15, U$55.10
Y2B: SV1.16, U$33.GATE
Y2B1: SV2.16, U$54.10
Y3A: SV1.17, U$11.GATE
Y3A1: SV2.17, U$55.8
Y3B: SV1.18, U$35.GATE
Y3B1: SV2.18, U$54.8
Y4A: SV1.19, U$13.GATE
Y4A1: SV2.19, U$55.7
Y4B: SV1.20, U$37.GATE
Y4B1: SV2.20, U$54.7
